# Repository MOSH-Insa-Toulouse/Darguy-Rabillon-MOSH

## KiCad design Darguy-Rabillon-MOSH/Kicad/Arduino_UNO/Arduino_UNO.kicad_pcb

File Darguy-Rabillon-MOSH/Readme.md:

# README - User guide

## Authors : 

	- Louis-Baptiste Rabillon
	- Ludovic Darguy

## Description : 

In the folder Darguy-Rabillon, you will find two main branches : 
	- Arduino
	- Kicad

Arduino contains source code of Arduino application reading gaz density value of the gaz sensor of our circuit.
First, the application connects to The Thing Network platform thanks to LoRa communication module. 
This application converts the gaz value and then sends it to The Thing Network Platform using TTN Library for Arduino.

Kicad contains all files of designed entities for the PCB conception. We created a library my_library where we added RN2483 module and Gaz sensor footprints and symbols.

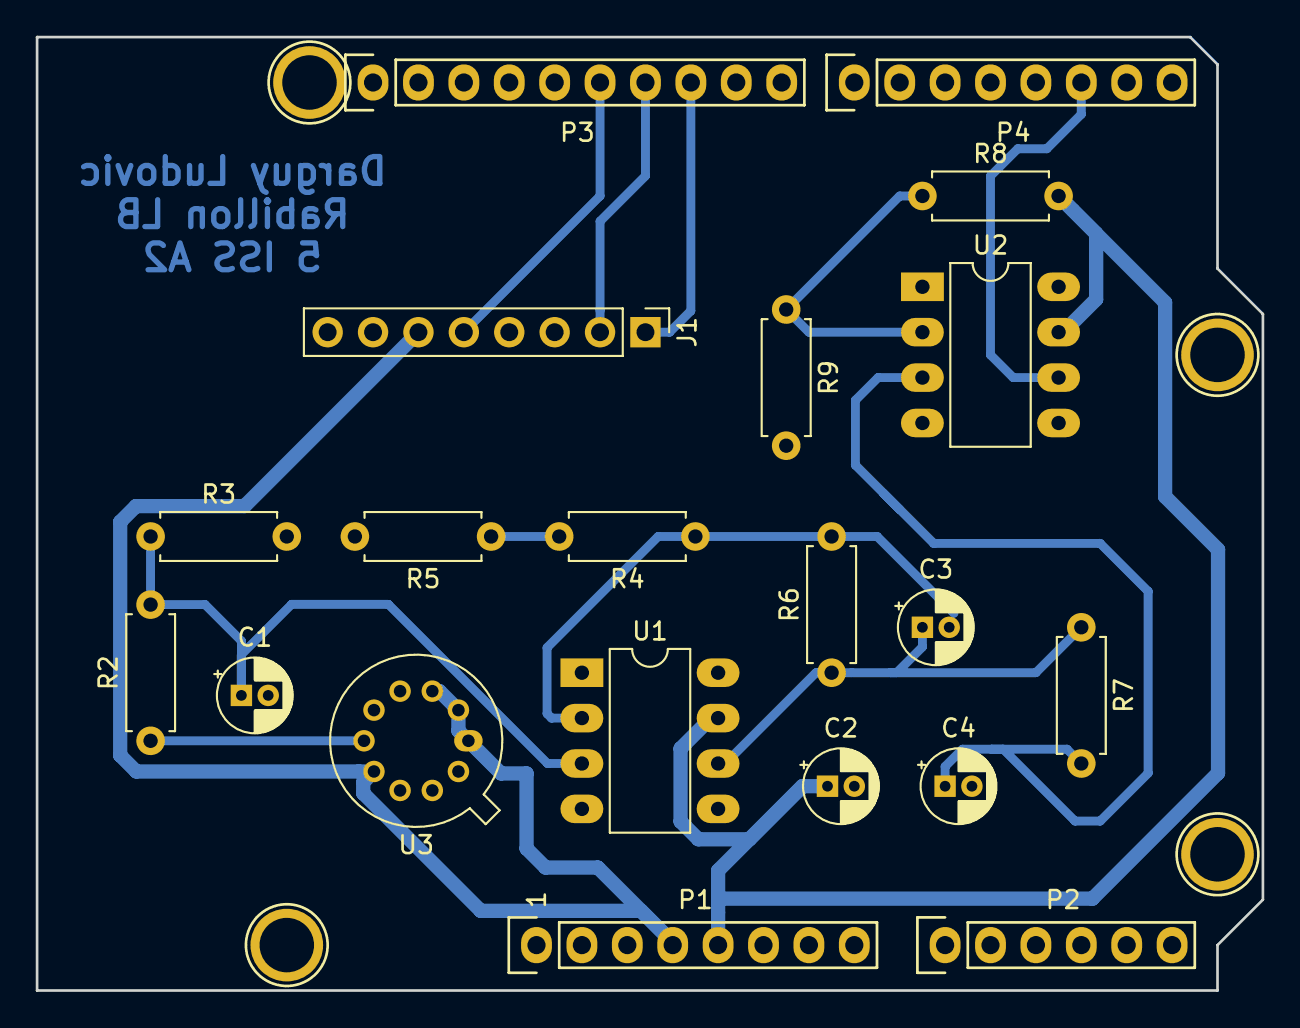
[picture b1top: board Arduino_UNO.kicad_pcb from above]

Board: 2 copper layers, 68.6 x 53.3 mm, 24 parts (0 on the bottom side), 14 nets.

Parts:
C1, C2, C3, C4: C; CP_Radial_D4.0mm_P1.50mm
J1: Conn_01x08_Male; PinHeader_1x08_P2.54mm_Vertical
P1: Power; Socket_Strip_Arduino_1x08
P2: Analog; Socket_Strip_Arduino_1x06
P3: Digital; Socket_Strip_Arduino_1x10
P4: Digital; Socket_Strip_Arduino_1x08
P5, P6, P7, P8: CONN_01X01; Arduino_1pin
R2, R3, R4, R5, R6, R7, R8, R9: R; R_Axial_DIN0207_L6.3mm_D2.5mm_P7.62mm_Horizontal
U1, U2: LTC1050; DIP-8_W7.62mm_LongPads
U3: Sensor_AIME; TO-5-10_Window

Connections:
+3V3: J1.6, P1.4, U3.1, U3.2, U3.3, U3.7
+5V: C2.1, P1.5, R8.2, U1.7, U2.7
/RST: J1.5, P3.6
/RX: J1.2, P3.7
/TX: J1.1, P3.8
AN0_Arduino: C4.1, R7.2, U2.3
GND: C1.2, C2.2, C4.2, J1.8, P1.6, P1.7, P3.4, R3.2, R5.2, R9.2, U1.4, U2.4, U3.4, U3.5, U3.8, U3.9, U3.10
unnamed: C1.1, R2.2, R3.1, U1.3
unnamed: C3.1, R6.1, R7.1, U1.6
unnamed: C3.2, R4.1, R6.2, U1.2
unnamed: R4.2, R5.1
unnamed: R8.1, R9.1, U2.2
VersR2: R2.1, U3.6
Vinterrupt: P4.6, U2.6

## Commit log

2020-01-22 final commit
